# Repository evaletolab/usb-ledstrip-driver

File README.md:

# usb-ledstrip-driver
===================
Connect a real light to your laptop without the need of external power. 

This simple device boost usb power to 24V and also,
- Small size, only 9x37 mm
- High Efficiency boost driver [LT3465][1] 81% at **(TODO)**
- quiescent current ?? **(TODO)**
- Control lighting with Attiny45/85 and arduino API **(TODO)**
- Ideal 24V ledstrip with ~66mA (RL=3[Ohms])switch current for ( **~1.58W** lighting).
 - note: The best LED efficiency is about 200LM for 2W with 3200K color temperature (Warm White)!!
- PWM for LED Control **(TODO)**
- IL=1/RL*(0.2-0.026*LN(EXP(0.2/0.026)/EXP(5/0.13)+1))

## Usual shot,

## Current developpement:
- Command the Ledstrip from USB [Virtual USB (V-USB)][2]
- Integrate [optiboot - a small boot loader -](http://code.google.com/p/optiboot/) and USB

## Long term,
- upgrade the driver with [LT3591][3], **~800mA** SWITCH current at USB line, load 24V  (**4W**)!!

## Known bugs

**THIS IS ALPHA SOFTWARE/HARDWARE AND SHOULD BE TREATED ACCORDINGLY.**
**IT IS FUN TO GET RUNNING, BUT EXPECT THINGS TO BE BROKEN.**

[1]: http://www.linear.com/product/LT3465
[2]: http://www.obdev.at/products/vusb/ 
[3]: http://www.linear.com/product/LT3591

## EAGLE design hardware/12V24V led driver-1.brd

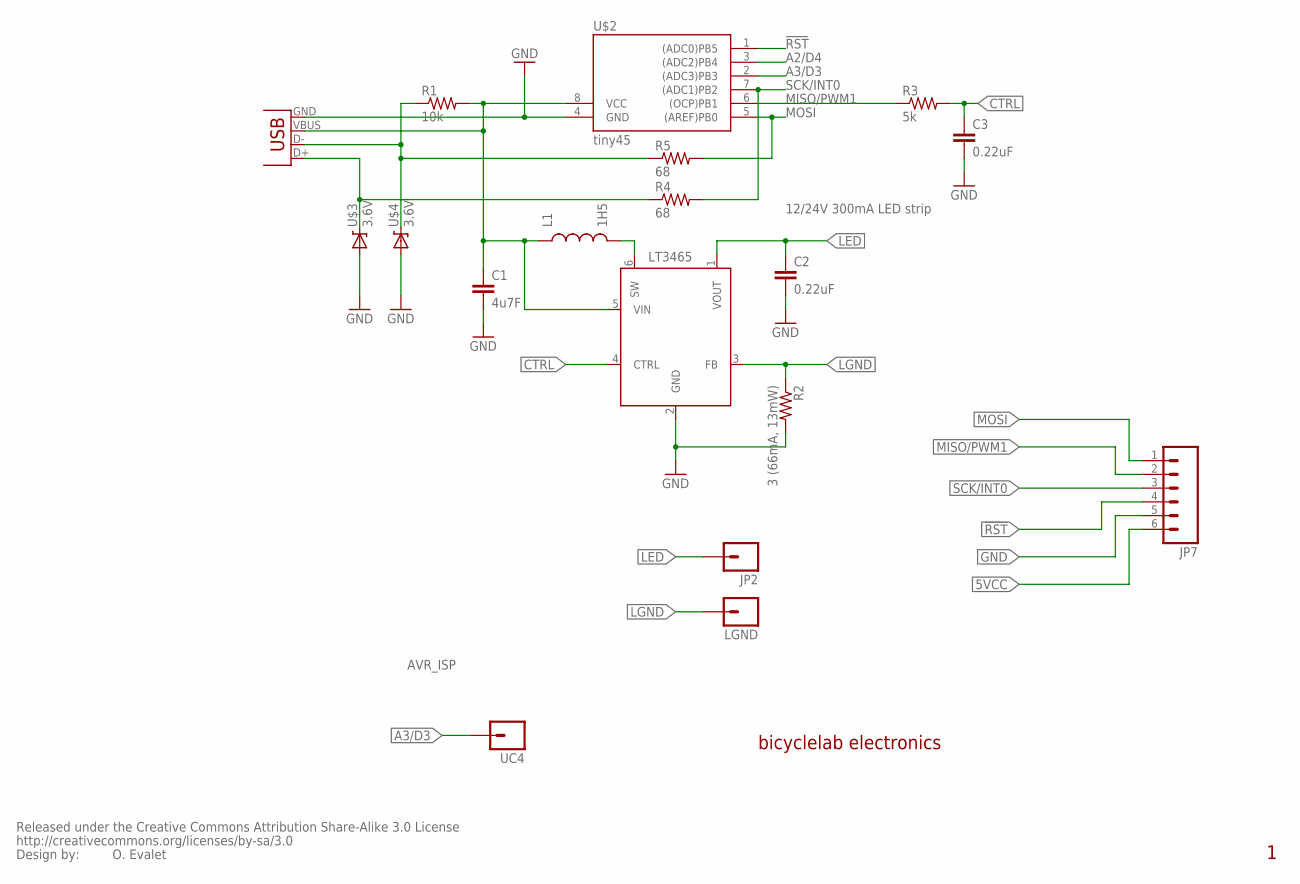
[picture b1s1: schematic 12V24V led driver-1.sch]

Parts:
C1: 4u7F; 0805
C2: 0.22uF; 0603-CAP
C3: 0.22uF; 0805
JP2: M01PTH; 1X01
JP7: M06EM406; EM406
L1: 1H5; 0805
LGND: M01PTH; 1X01
MISB-SW-5B: MISB-SW-5B; USB-MICROB
R1: 10k; 0805
R2: 3 (66mA, 13mW); 1206
R3: 5k; 0805
R4, R5: 68; 0805
U$1: LT365; TSOT23-6_DDC
U$2: tiny45; SOIC8
U$3, U$4: 3.6V; SOD-323
U$5: CREATIVE_COMMONS
UC4: M01SMD-4.5X1.5; PAD-1.5X4.5

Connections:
5VCC: C1.1, JP7.6, L1.1, MISB-SW-5B.VBUS, R1.2, U$1.5 (VIN), U$2.8 (VCC)
!RST: JP7.4, U$2.1 ((ADC0)PB5)
A2/D4: U$2.3 ((ADC2)PB4)
A3/D3: U$2.2 ((ADC3)PB3), UC4.P$1
CTRL: C3.1, R3.2, U$1.4 (CTRL)
GND: C1.2, C2.2, C3.2, JP7.5, MISB-SW-5B.GND, R2.2, U$1.2 (GND), U$2.4 (GND), U$3.2 (A), U$4.2 (A)
LED: C2.1, JP2.1, U$1.1 (VOUT)
LGND: LGND.1, R2.1, U$1.3 (FB)
MISO/PWM1: JP7.2, R3.1, U$2.6 ((OCP)PB1)
MOSI: JP7.1, R5.2, U$2.5 ((AREF)PB0)
unnamed: MISB-SW-5B.D+, R4.1, U$3.1 (C)
unnamed: MISB-SW-5B.D-, R1.1, R5.1, U$4.1 (C)
unnamed: L1.2, U$1.6 (SW)
SCK/INT0: JP7.3, R4.2, U$2.7 ((ADC1)PB2)

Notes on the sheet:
bicyclelab electronics
O. Evalet
12/24V 300mA LED strip
AVR_ISP

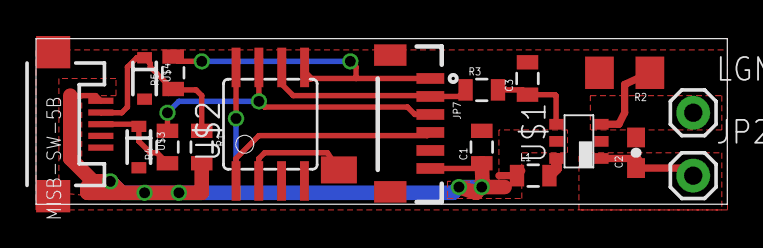
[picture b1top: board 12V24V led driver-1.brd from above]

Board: 2 copper layers, 38.4 x 9.2 mm, 19 parts (0 on the bottom side), 13 nets.

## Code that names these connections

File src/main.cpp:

#include <WProgram.h>
#include <avr/sleep.h>
#include <avr/power.h>

 /**
  * main.cpp - 
  * Copyright (c) 2012 O. Evalet.  All right reserved.
  *
  * This library is free software; you can redistribute it and/or
  * modify it under the terms of the GNU Lesser General Public
  * License as published by the Free Software Foundation; either
  * version 3 of the License, or (at your option) any later version.
  * 
  * This library is distributed in the hope that it will be useful,
  * but WITHOUT ANY WARRANTY; without even the implied warranty of
  * MERCHANTABILITY or FITNESS FOR A PARTICULAR PURPOSE.  See the GNU
  * Lesser General Public License for more details.
  * 
  * You should have received a copy of the GNU Lesser General Public
  * License along with this library; if not, write to the Free Software
  * Foundation, Inc., 51 Franklin St, Fifth Floor, Boston, MA  02110-1301  USA
  **/

// ATMEL ATTINY45 / ARDUINO
//
//                           +-\/-+
//  Ain0       (D  5)  PB5  1|    |8   VCC
//  Ain3       (D  3)  PB3  2|    |7   PB2  (D  2)  INT0  Ain1
//  Ain2       (D  4)  PB4  3|    |6   PB1  (D  1)        pwm1
//                     GND  4|    |5   PB0  (D  0)        pwm0
//                           +----+

// LED PWM to digital pin 0
#define LED 0



//
// energy saver 
void prescaler(byte mode){
  cli();
  CLKPR=bit(CLKPCE);
  CLKPR=mode;
  sei();
}

//
// energy saver 
// prescale of 2² (4)  5,3mA with a328p (prescale 0 => 8,5mA)
void sleep(int t){
  prescaler(2);
  long l=millis()+t/4;
  while(millis()<l){
  	set_sleep_mode(SLEEP_MODE_IDLE);
  	sleep_mode();
  }
  prescaler(0);
}



void setup()  { 
} 


void loop()  { 
  for(int fadeValue = 0 ; fadeValue <= 255; fadeValue +=5) { 
    // sets the value (range from 0 to 255):
    analogWrite(LED, fadeValue);         
    // wait for 30 milliseconds to see the dimming effect    
    sleep(30);                            
  } 

  for(int fadeValue = 255 ; fadeValue >= 0; fadeValue -=5) { 
    // sets the value (range from 0 to 255):
    analogWrite(LED, fadeValue);         
    // wait for 30 milliseconds to see the dimming effect    
    sleep(30);                            
  } 
}

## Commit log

2012-04-23 more readme
2012-05-02 fix bug, add usb i/o
2012-12-25 just cleaning
2012-12-25 usb ctrl imp.

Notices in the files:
parts and their libraries:
SparkFun: Released under the Creative Commons Attribution Share-Alike 3.0 License
SparkFun: http://creativecommons.org/licenses/by-sa/3.0
